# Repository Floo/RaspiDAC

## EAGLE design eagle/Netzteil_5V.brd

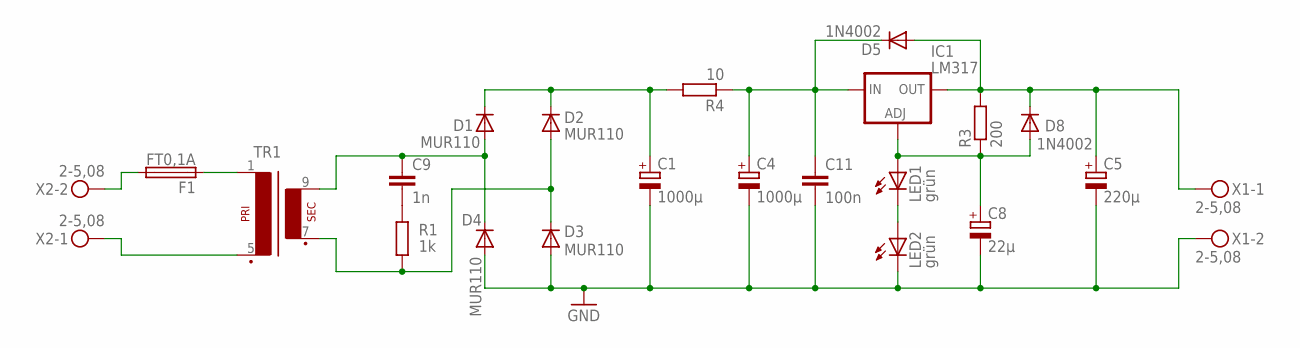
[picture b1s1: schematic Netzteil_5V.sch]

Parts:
C1, C4: 1000µ; E5-13
C5: 220µ; E3,5-8
C8: 22µ; E2-5
C9: 1n; C050-045X075
C11: 100n; C050-025X075
D1, D2, D3, D4: MUR110; DO41-10
D5, D8: 1N4002; DO41-10
F1: FT0,1A; 19560
IC1: LM317; 317TS
LED1, LED2: grün; LED3MM
R1: 1k; 0207/10
R3: 200; 0207/10
R4: 10; 0617V
TR1: EI38-1
X1, X2: 2-5,08; MKDSN1,5/2-5,08

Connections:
GND: C1.-, C4.-, C5.-, C8.-, C11.2, D3.A, D4.A, LED2.K (C), X1.2
unnamed: F1.2, X2.2
unnamed: F1.1, TR1.1
unnamed: TR1.5 (P2), X2.1
unnamed: LED1.K (C), LED2.A
unnamed: C9.2, R1.2
unnamed: C9.1, D1.A, D4.C, TR1.9 (S4)
unnamed: D2.A, D3.C, R1.1, TR1.7 (S3)
unnamed: C1.+, D1.C, D2.C, R4.2
unnamed: C4.+, C11.1, D5.C, IC1.3 (IN), R4.1
unnamed: C8.+, D8.A, IC1.1 (ADJ), LED1.A, R3.1
unnamed: C5.+, D5.A, D8.C, IC1.2 (OUT), R3.2, X1.1

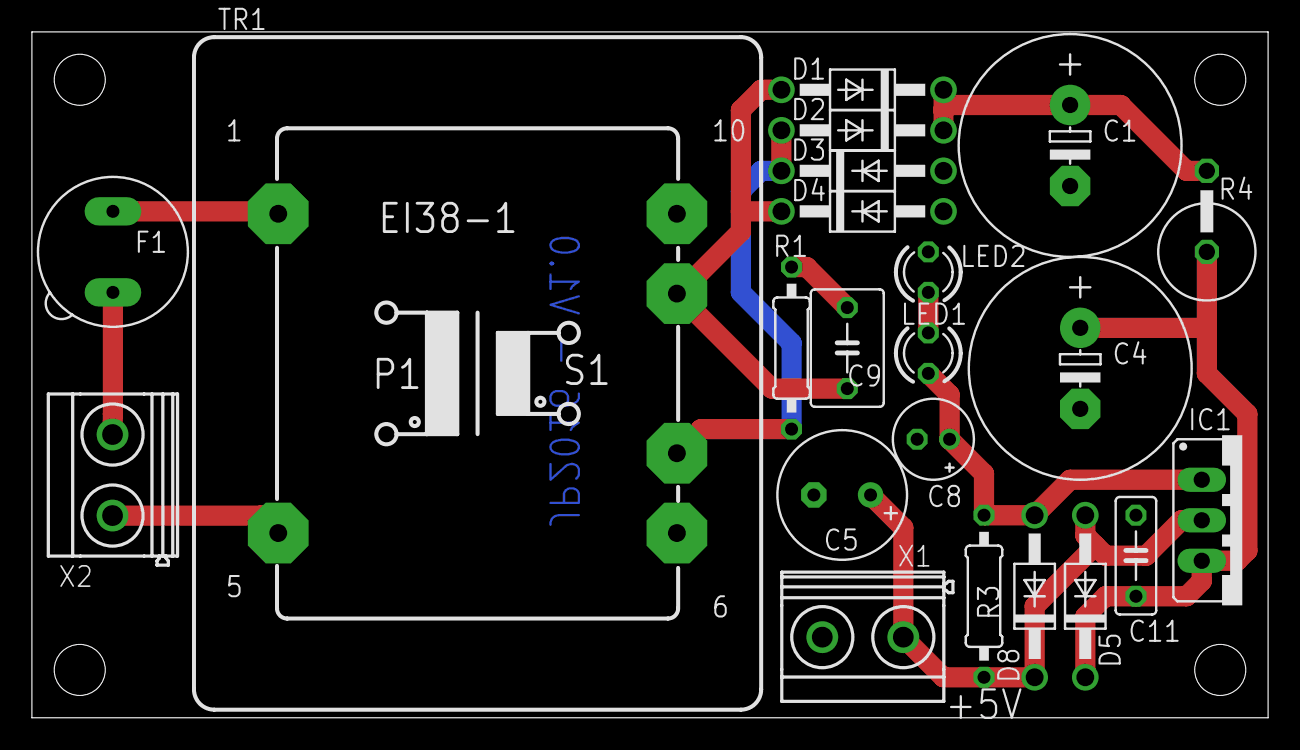
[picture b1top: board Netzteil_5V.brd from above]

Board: 2 copper layers, 77.5 x 43.0 mm, 22 parts (0 on the bottom side), 12 nets.

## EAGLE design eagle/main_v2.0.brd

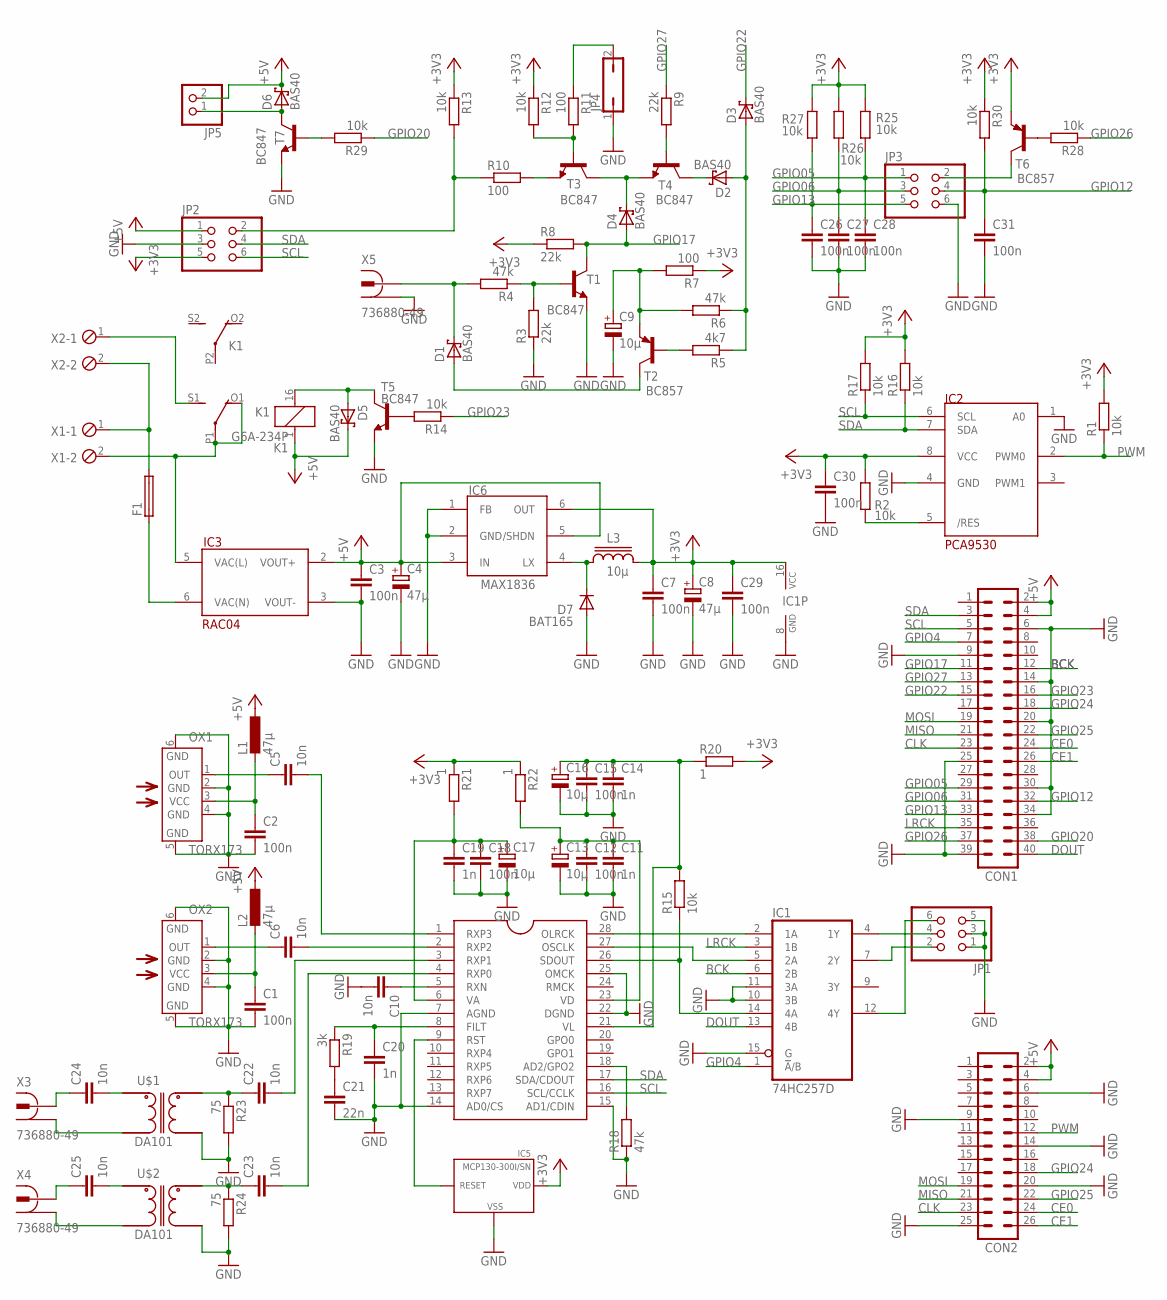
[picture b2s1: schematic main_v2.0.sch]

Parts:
C1, C2, C3, C7, C12, C15, C18, C26, C27, C28, C29, C30, C31: 100n; C0805
C4, C8: 47µ; CT3528
C5, C6, C10, C22, C23, C24, C25: 10n; C0805
C9, C13, C16, C17: 10µ; CT3216
C11, C14, C19, C20: 1n; C0805
C21: 22n; C0805
CON1: MA20-2
CON2: MA13-2
D1, D2, D3, D4, D5, D6: BAS40; SOT23
D7: BAT165; SOD-323F
F1: 19560
IC1: 74HC257D; SO16
IC2: PCA9530; SOIC-8
IC3: RAC04; RECOM-RAC04
IC4: CS8416; SO28L
IC5: MCP130-300I/SN; SOT-23
IC6: MAX1836; SOT23-6L
JP1, JP2, JP3: PINHD-2X3; 2X03
JP4: JP1Q; JP1
JP5: PINHD-1X2; 1X02
K1: G6A-234P
L1, L2: 47µ; C1210
L3: 10µ; LPS4018
OX1, OX2: TORX173
R1, R2, R12, R13, R14, R15, R16, R17, R25, R26, R27, R28, R29, R30: 10k; R0805
R3, R8, R9: 22k; R0805
R4, R6, R18: 47k; R0805
R5: 4k7; R0805
R7, R10, R11: 100; R0805
R19: 3k; R0805
R20, R21, R22: 1; R0805
R23, R24: 75; R0805
T1, T3, T4, T5, T7: BC847; SOT23-BEC
T2, T6: BC857; SOT23-BEC
U$1, U$2: DA101; 6PIN-DIL
X1, X2: 2POL500
X3, X4, X5: 736880-49

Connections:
+3V3: C7.1, C8.+, C29.1, C30.1, IC1.16 (VCC), IC2.8 (VCC), IC5.2 (VDD), IC6.6 (OUT), JP2.5, L3.2, R1.2, R2.2, R7.1, R8.1, R12.1, R13.1, R16.2, R17.2, R20.2, R21.1, R22.1, R25.1, R26.1, R27.1, R30.1, T6.E
+5V: C3.1, C4.+, CON1.2, CON1.4, CON2.2, CON2.4, D5.3 (C), D6.3 (C), IC3.2 (VOUT+), IC6.3 (IN), IC6.5 (/SHDN), JP2.1, JP5.2, K1.1, L1.1, L2.1
BCK: CON1.12, IC1.6 (2B)
CE0: CON1.24, CON2.24
CE1: CON1.26, CON2.26
CLK: CON1.23, CON2.23
DOUT: CON1.40, IC1.13 (4B)
GND: C1.2, C2.2, C3.2, C4.-, C7.2, C8.-, C9.-, C10.2, C11.2, C12.2, C13.-, C14.2, C15.2, C16.-, C17.-, C18.2, C19.2, C20.2, C21.2, C26.2, C27.2, C28.2, C29.2, C30.2, C31.2, CON1.6, CON1.9, CON1.14, CON1.20, CON1.25, CON1.30, CON1.34, CON1.39, CON2.6, CON2.9, CON2.14, CON2.20, CON2.25, D7.A, IC1.8 (GND), IC1.10 (3B), IC1.11 (3A), IC1.15 (G), IC2.1 (A0), IC2.4 (GND), IC3.3 (VOUT-), IC4.7 (AGND), IC4.14 (AD0/CS), IC4.15 (AD1/CDIN), IC4.22 (DGND), IC4.25 (OMCK), IC5.3 (VSS), IC6.1 (FB), IC6.2 (GND), JP1.1, JP1.3, JP1.5, JP2.3, JP3.6, JP4.1, OX1.2 (GND), OX1.4 (GND), OX1.5 (GND), OX1.6 (GND), OX2.2 (GND), OX2.4 (GND), OX2.5 (GND), OX2.6 (GND), R3.1, R18.1, R23.2, R24.2, T1.E, T5.E, T7.E, U$1.4, U$2.4, X5.1, X5.1@1 (1), X5.1@2 (1)
GPIO4: CON1.7, IC1.1 (!A!/B)
GPIO05: C28.1, CON1.29, JP3.1, R25.2
GPIO06: C27.1, CON1.31, JP3.3, R26.2
GPIO12: C31.1, CON1.32, JP3.4, R30.2
GPIO13: C26.1, CON1.33, JP3.5, R27.2
GPIO17: CON1.11, D4.1 (A), R8.2, T1.C
GPIO20: CON1.38, R29.1
GPIO22: CON1.15, D3.3 (C)
GPIO23: CON1.16, R14.1
GPIO24: CON1.18, CON2.18
GPIO25: CON1.22, CON2.22
GPIO26: CON1.37, R28.1
GPIO27: CON1.13, R9.1
LRCK: CON1.35, IC1.3 (1B)
MISO: CON1.21, CON2.21
MOSI: CON1.19, CON2.19
unnamed: C11.1, C12.1, C13.+, IC4.23 (VD), R22.2
unnamed: IC1.2 (1A), IC4.28 (OLRCK)
unnamed: IC1.5 (2A), IC4.27 (OSCLK)
unnamed: IC1.14 (4A), IC4.26 (SDOUT), R15.1
unnamed: IC4.9 (RST), IC5.1 (RESET)
unnamed: IC2.5 (/RES), R2.1
unnamed: F1.1, IC3.6 (VAC(N))
unnamed: C17.+, C18.1, C19.1, IC4.6 (VA), R21.2
unnamed: C6.1, OX2.1 (OUT)
unnamed: C5.1, OX1.1 (OUT)
unnamed: C6.2, IC4.2 (RXP2)
unnamed: C5.2, IC4.1 (RXP3)
unnamed: IC3.5 (VAC(L)), K1.O1 (O), K1.P1, X1.2
unnamed: R3.2, R4.1, T1.B
unnamed: JP4.2, R11.1
unnamed: D1.1 (A), T2.C
unnamed: D1.3 (C), R4.2, X5.2
unnamed: C9.+, R6.2, R7.2, T2.E
unnamed: R5.2, T2.B
unnamed: D2.1 (A), D3.1 (A), R5.1, R6.1
unnamed: D4.3 (C), T3.C, T4.E
unnamed: R10.2, T3.E
unnamed: R11.2, R12.2, T3.B
unnamed: R9.2, T4.B
unnamed: D2.3 (C), T4.C
unnamed: IC1.7 (2Y), JP1.2
unnamed: IC1.4 (1Y), JP1.4
unnamed: D7.C, IC6.4 (LX), L3.1
unnamed: JP2.2, R10.1, R13.2
unnamed: C10.1, IC4.5 (RXN)
unnamed: IC4.18 (AD2/GPO2), R18.2
unnamed: C14.1, C15.1, C16.+, IC4.21 (VL), R15.2, R20.1
unnamed: D5.1 (A), K1.16 (2), T5.C
unnamed: R14.2, T5.B
unnamed: C22.1, R23.1, U$1.6
unnamed: C20.1, IC4.8 (FILT), R19.1
unnamed: C21.1, R19.2
unnamed: C22.2, IC4.3 (RXP1)
unnamed: C23.2, IC4.4 (RXP0)
unnamed: C23.1, R24.1, U$2.6
unnamed: C24.2, U$1.1
unnamed: U$1.3, X3.1, X3.1@1 (1), X3.1@2 (1)
unnamed: C24.1, X3.2
unnamed: C25.2, U$2.1
unnamed: U$2.3, X4.1, X4.1@1 (1), X4.1@2 (1)
unnamed: C25.1, X4.2
unnamed: R28.2, T6.B
unnamed: K1.S1 (S), X2.1
unnamed: F1.2, X1.1, X2.2
unnamed: C2.1, L1.2, OX1.3 (VCC)
unnamed: C1.1, L2.2, OX2.3 (VCC)
unnamed: D6.1 (A), JP5.1, T7.C
unnamed: IC1.12 (4Y), JP1.6
unnamed: JP3.2, T6.C
unnamed: R29.2, T7.B
PWM: CON2.12, IC2.2 (PWM0), R1.1
SCL: CON1.5, IC2.6 (SCL), IC4.16 (SCL/CCLK), JP2.6, R17.1
SDA: CON1.3, IC2.7 (SDA), IC4.17 (SDA/CDOUT), JP2.4, R16.1

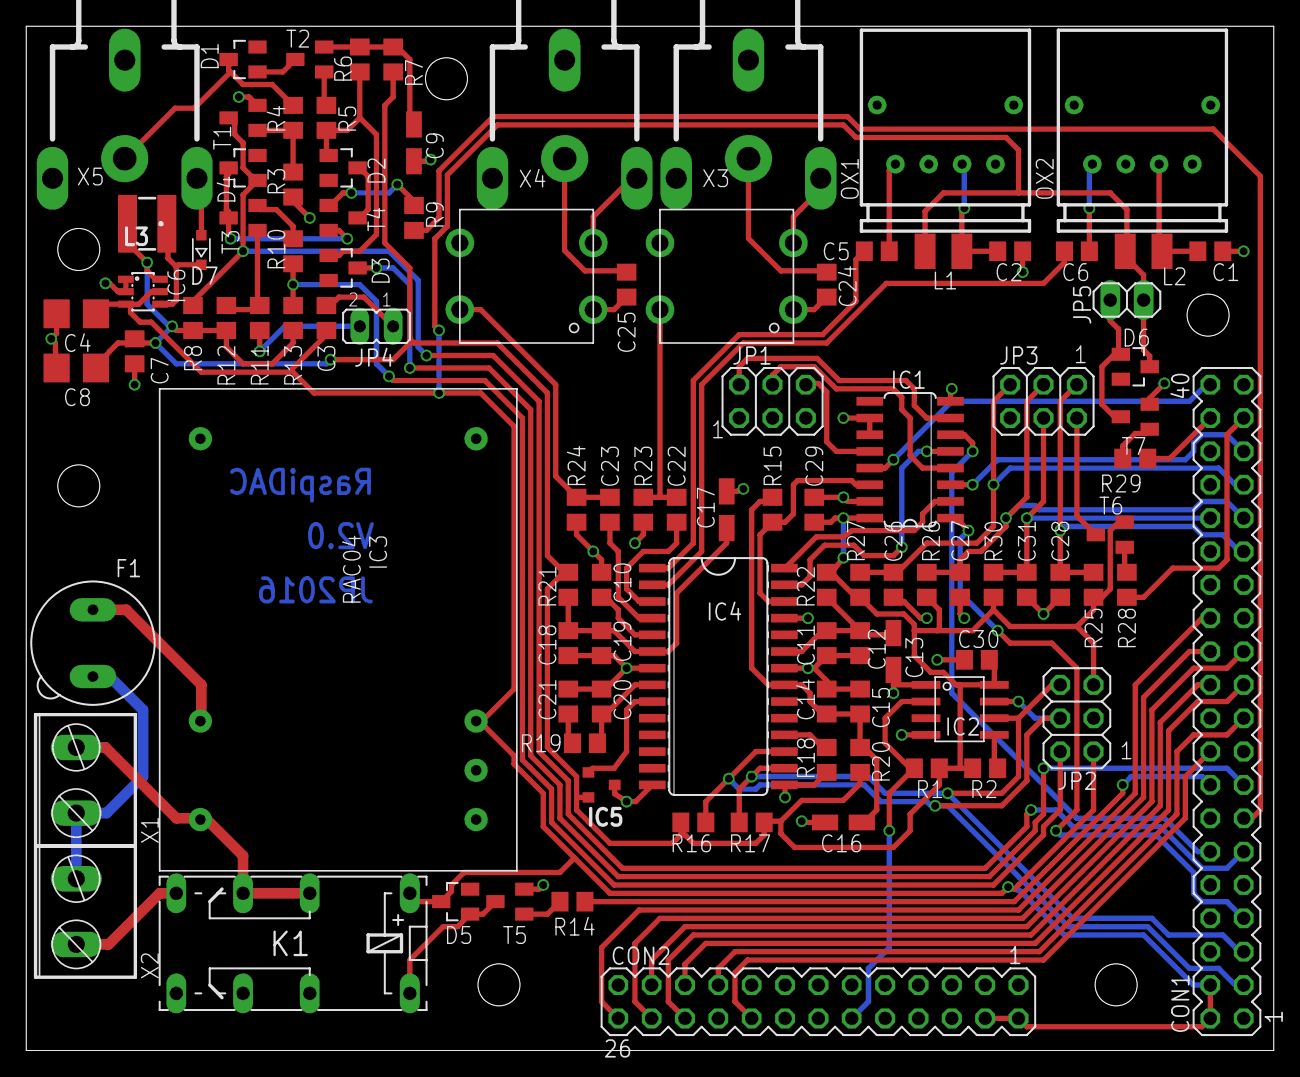
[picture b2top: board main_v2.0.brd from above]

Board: 2 copper layers, 95.0 x 78.0 mm, 102 parts (0 on the bottom side), 82 nets.

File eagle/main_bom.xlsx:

Anzahl | Part | Value | Package | Lieferant | Best.-Nr. | Preis | Preis pro Einheit
4 | C11, C14, C19, C20 | 1n NP0 | 0805 | Segor | 1n0-0805-NP0 | 0.05 | 0.2
7 | C5, C6, C10, C22, C23, C24, C25 | 10n | 0805 | Segor | 10n-0805-X7R | 0.05 | 0.35000000000000003
1 | C21 | 22n X7R | 0805 | Segor | 22n-0805-X7R | 0.05 | 0.05
13 | C1, C2, C3, C7, C12, C15, C18, C26, C27, C28, C29, C30, C31 | 100n | 0805 | Segor | 100n-0805-X7R | 0.05 | 0.65
4 | C9, C13, C16, C17 | 10µ | 3216 | Conrad | 458293 | 0.3 | 1.2
2 | C4, C8 | 47µ/10V | 3528 | Conrad | 458307 | 0.31 | 0.62
2 | L1, L2 | 47µH | 1210 | Reichelt | LQH3C 47µ | 0.14000000000000001 | 0.28000000000000003
1 | L3 | 10µH | 1608
3 | R20, R21, R22 | 1R | 0805 | Segor | 1R0-0805-1% | 3.7999999999999999E-2 | 0.11399999999999999
2 | R23, R24 | 75R | 0805 | Segor | 75R-0805-1% | 3.7999999999999999E-2 | 7.5999999999999998E-2
3 | R7, R10, R11 | 100R | 0805 | Segor | 100R-0805-1% | 3.7999999999999999E-2 | 0.11399999999999999
1 | R19 | 3k | 0805 | Segor | 3k0-0805-1% | 0.04 | 0.04
1 | R5 | 4k7 | 0805 | Segor | 4k7-0805-1% | 0.04 | 0.04
13 | R1, R2, R12, R13, R14, R15, R16, R17, R25, R26, R27, R28, R30 | 10k | 0805 | Segor | 10k-0805-1% | 3.7999999999999999E-2 | 0.49399999999999999
3 | R3, R8, R9 | 22k | 0805 | Segor | 22k-0805-1% | 3.7999999999999999E-2 | 0.11399999999999999
3 | R4, R6, R18 | 47k | 0805 | Segor | 47k-0805-1% | 3.7999999999999999E-2 | 0.11399999999999999
4 | T1, T3, T4, T5 | BC847 | SOT23 | Reichelt | BC 847C SMD | 0.04 | 0.16
2 | T2, T6 | BC857 | SOT23 | Reichelt | BC 857C SMD | 0.04 | 0.08
2 | U1, U2 | DA101 |  | Segor | DA101C | 3.2 | 6.4
3 | X3, X4, X5 | Cinch-Buchse |  | Conrad | 736899 | 1.47 | 4.41
1 | IC1 | 74CBTLV3257 | SO-16 | vorhanden |  |  | 0
1 | IC2 | PCA9530 | SO-8 | Reichelt | PCA 9530 D | 1.45 | 1.45
1 | IC4 | CS8416 | SO-28 | Cirrus | Sample | 0 | 0
1 | IC3 | RAC04-05SC/230 |  | Recom | Sample | 0 | 0
1 | IC6 | MAX1724EZK33 |  | Maxim | Sample | 0 | 0 | durch Step-Down Wandler ersetzen, MAX1921
1 | IC5 | MCP130-300 | SOT23 | Conrad | 1085790 | 0.65 | 0.65
1 | K1 | G6A 5V |  | Conrad | 503801 | 4.2 | 4.2
2 | OX1, OX2 | TORX173 |  | vorhanden |  | 0 | 0 | Ersatztyp TORX1952, lieferbar bei Segor
5 | D1, D2, D3, D4, D5 | BAS16 | SOT23 | Conrad | 162030 | 7.0000000000000007E-2 | 0.35000000000000003
1 | F1 | MIK-TRÄGE 0,1A |  | Reichelt | MIK-TRÄGE 0,1A | 0.32 | 0.32
2 |  | Pfostenverbinder RM2,54 2x13 |  | Conrad | 742185 | 0.56000000000000005 | 1.1200000000000001
2 |  | Pfostenverbinder RM2,54 2x20 |  | Conrad | 742221 | 0.74 | 1.48
1 |  | OS-0038N |  | Conrad | 184301 | 0.99 | 0.99
 |  |  |  |  |  |  | 26.065999999999999

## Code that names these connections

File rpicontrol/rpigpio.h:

#ifndef RPIGPIO_H
#define RPIGPIO_H

#include <QObject>
#include <wiringPi.h>
#include <wiringPiI2C.h>
#include <QDebug>

#define GPIO04 4    //Input-Select
#define GPIO27 27   //RC5-direct
#define GPIO05 5    //Taster1
#define GPIO06 6    //Taster2
#define GPIO13 13   //Taster3
#define GPIO12 12   //Taster4
#define GPIO23 23   //Relais
#define GPIO26 26   //LED_Power

#define PCA9530 0x60  //I2C Adresse des LED-PWM
#define CS8416  0x10  //I2C Adresse des SPDIF-Decoders

// -- CS8416 I2C COMMANDS

#define CS_CMD_IDVER            0x7f
#define CS_CMD_SER_AUDIO_FORMAT 0x05
#define CS_CMD_CONTROL0         0x00
#define CS_CMD_CONTROL1         0x01
#define CS_CMD_CONTROL2         0x02
#define CS_CMD_CONTROL3         0x03
#define CS_CMD_CONTROL4         0x04

#define CS_CMD_REC_CHAN_STAT     0x0A
#define CS_CMD_AUDIO_FORMAT_DET  0x0B
#define CS_CMD_REC_ERROR         0x0C
#define CS_CMD_IRQ_STAT          0x0D

#define LED_ON     0
#define LED_OFF    1
#define LED_BLINK  100
#define REL_ON     1
#define REL_OFF    0
#define RC5_DIRECT_ON  1
#define RC5_DIRECT_OFF 0
#define INPUT_UPNP   0
#define INPUT_DAC    1

#define BACKLIGHT_MAX   0
#define BACKLIGHT_DIMM  200
#define BACKLIGHT_MIN   255


class RPiGPIO : public QObject
{
    Q_OBJECT

public:
    RPiGPIO();
    ~RPiGPIO();

    int getLED();
    int getRC5direct();
    int getRelais();
    int getInputSelect();
    void pca9530Setup();
    void cs8416Setup();


public slots:
    void toggleLED();
    void setLED(int);
    void setRC5direct(int);
    void setRelais(int);
    void setInputSelect(int);
    void setBacklight(int);
    void setCS8416InputSelect(int);
    void getCS8416ID();
    void getCS8416Reg(int);

signals:
    void taster1();
    void taster2();
    void taster3();
    void taster4();

private:
    class Internal;
    Internal *m;
    int fd_pca9530 = 0;
    int fd_cs8416 = 0;
};

#endif // RPIGPIO_H

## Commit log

2015-07-15 Projekt neu zusammengestellt mit Bezug auf upstream Repository
2015-07-15 Update AUTHORS
2015-07-15 Feinschliff bei Projektzusammenstellung
2015-07-17 Eaegle-Files mit Versionsnummern versehen und Version 2.0 hinzugefügt
2015-07-17 Frontplatte überprüft und bemaßt
2015-07-29 nur GUI
2015-07-31 Add Schematics_v1.0.pdf
2015-08-07 Bestückungsplan aktualisiert
2015-11-14 neue Fenster hinzugefuegt
2015-11-16 Rückplatte designed
2015-11-16 Schriften in Resource-File
2015-11-17 neue Logos designed
2015-11-18 Settings
2015-12-30 Radio erweitert
2016-01-26 neues Interface zu upplay, OHRadio wird verwendet
2016-01-28 GUI erweitert
2016-02-03 GUI und Menu eingebaut
2016-02-09 Erzeugung der RadioList ohne zusätzliches SIGNAL in application.cpp
2016-02-13 Kommunikation mit hsGUI
2016-02-14 Taster über GPIO laufen
2016-02-15 Ablaufsteuerung verbessert
2016-02-15 Ticker und AlbumArt verbessert
2016-02-15 Shutdown
2016-02-16 GUI verbessert
2016-02-17 UDP Initialisierung
2016-02-19 GPIO Tasten
2016-02-23 Eagle-Files: V2.0, zusätzlichen Ausgang für Relais eingebaut
2016-02-23 Start-Skripte hinzugefügt
2016-02-29 lirc-Klassen erstellt
2016-02-29 Umstellung auf Subtree-Projekt
2016-02-29 Umstellung auf Subtree-Projekt - Feinschliff und upplay.cpp umbenannt in RaspiDAC.cpp
2016-03-02 NetAPI auf QHash umgestellt, Beginn mit LIRC Implementierung
2016-03-04 LircTest hinzugefügt, ohne QSocketNotifier
2016-03-06 LIRC Empfang funktioniert
2016-03-07 Eagle V2.0: 3.3V Step-Down-Wandler ersetzt und Fehler behoben. Keine weiteren Anpassungen mehr nötig.
2016-03-07 Eagle: Bibliotheken hinzugefügt
2016-03-07 LIRC send geschrieben, noch nicht getestet
2016-03-08 LIRC send noch nicht ganz vollständig
2016-03-09 LIRC läuft, Senden und Empfangen
2016-03-10 Simulation des IR-Interface
2016-03-10 Entwurf Konfiguration in CSettingStorage Entwurf I2C für Lichtsensor
2016-03-11 Repeat für LircSend eingefügt und unterschiedliche PULSE_LENGTH und SPACE_LENGTH
2016-03-11 Lirc kleine Änderungen
2016-03-11 LircDevice repeated send getestet
2016-03-11 Sytaxfehler behoben, noch nicht getestet
2016-03-13 conf-File, Output-Relais, Helligkeitssensor auslesen
2016-04-11 Eagle Netzteilplatinen erstellt
2016-04-11 Feinschliff Eagle Daten
2016-04-12 Helligkeitssteuerung und Änderungen an der Oberfläche
